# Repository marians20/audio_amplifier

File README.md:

# audio_amplifier

## PCB Manufacturing Providers

- [PCB Phoenix](https://phoenixpcb.ro/) – Au experiență solidă și pot produce circuite rigide, inclusiv plăci foarte lungi, de până la 2400 mm.

- [PCB-ELECTRA](https://www.pcb-electra.ro/) – Parte a Grupului ELECTRA, oferă plăci de circuite imprimate personalizate și are certificare UL.

- [Multi Circuit Boards](https://www.multi-circuit-boards.eu/en/index.html)

- [Price calculator](https://portal.multi-circuit-boards.eu/)

- Eashub – Oferă servicii complete, de la prototipuri la producție și asamblare PCB.

- PCBandAssembly – Se laudă cu livrare expres în 24 de ore și o politică de rambursare 100% pentru defecte de calitate

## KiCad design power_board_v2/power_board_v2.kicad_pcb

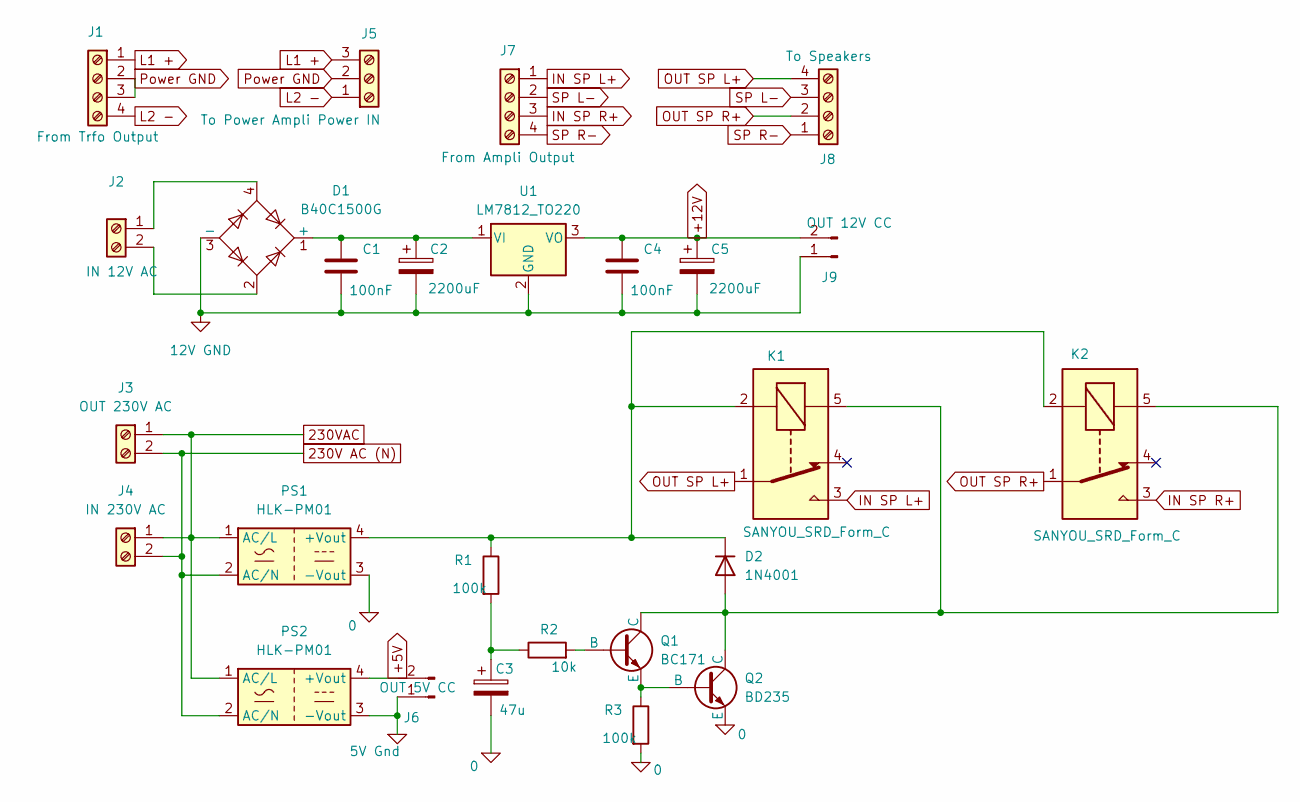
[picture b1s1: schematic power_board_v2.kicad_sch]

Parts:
C1, C4: 100nF; C_Disc_D8.0mm_W2.5mm_P5.00mm
C2, C5: 2200uF; CP_Radial_D12.5mm_P5.00mm
C3: 47u; CP_Radial_D5.0mm_P2.50mm
D1: B40C1500G; Diode_Bridge_Round_D9.8mm
D2: 1N4001; D_DO-41_SOD81_P10.16mm_Horizontal
J1: From Trfo Output; TerminalBlock_Altech_AK300-4_P5.00mm
J2: IN 12V AC; TerminalBlock_Altech_AK300-2_P5.00mm
J3: OUT 230V AC; TerminalBlock_Altech_AK300-2_P5.00mm
J4: IN 230V AC; TerminalBlock_Altech_AK300-2_P5.00mm
J5: To Power Ampli Power IN; TerminalBlock_Altech_AK300-3_P5.00mm
J6: OUT 5V CC; JST_XH_B2B-XH-A_1x02_P2.50mm_Vertical
J7: From Ampli Output; TerminalBlock_Altech_AK300-4_P5.00mm
J8: To Speakers; TerminalBlock_Altech_AK300-4_P5.00mm
J9: OUT 12V CC; JST_XH_B2B-XH-A_1x02_P2.50mm_Vertical
K1, K2: SANYOU_SRD_Form_C; Relay_SPDT_SANYOU_SRD_Series_Form_C
PS1, PS2: HLK-PM01; Converter_ACDC_Hi-Link_HLK-PMxx
Q1: BC171; TO-92L_Inline_Wide
Q2: BD235; TO-126-3_Vertical
R1, R3: 100k; R_Axial_DIN0207_L6.3mm_D2.5mm_P15.24mm_Horizontal
R2: 10k; R_Axial_DIN0207_L6.3mm_D2.5mm_P15.24mm_Horizontal
U1: LM7812_TO220; TO-220-3_Vertical

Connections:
0: C3.2, PS1.3 (-Vout), Q2.3 (E), R3.2
5V Gnd: J6.1, PS2.3 (-Vout)
12V GND: C1.2, C2.2, C4.2, C5.2, D1.3 (-), J9.1, U1.2 (GND)
230V AC (N): J3.2, J4.2, PS1.2 (AC/N), PS2.2 (AC/N)
230VAC: J3.1, J4.1, PS1.1 (AC/L), PS2.1 (AC/L)
+5V: J6.2, PS2.4 (+Vout)
+12V: C4.1, C5.1, J9.2, U1.3 (VO)
IN SP L+: J7.1, K1.3
IN SP R+: J7.3, K2.3
L1 +: J1.1, J5.3
L2 -: J1.4, J5.1
unnamed: C3.1, R1.2, R2.1
unnamed: C1.1, C2.1, D1.1 (+), U1.1 (VI)
unnamed: D2.2 (A), K1.5, K2.5, Q1.1 (C), Q2.1 (C)
unnamed: D2.1 (K), K1.2, K2.2, PS1.4 (+Vout), R1.1
unnamed: D1.4, J2.1
unnamed: D1.2, J2.2
unnamed: Q1.2 (B), R2.2
unnamed: Q1.3 (E), Q2.2 (B), R3.1
OUT SP L+: J8.4, K1.1
OUT SP R+: J8.2, K2.1
Power GND: J1.2, J1.3, J5.2
SP L-: J7.2, J8.3
SP R-: J7.4, J8.1

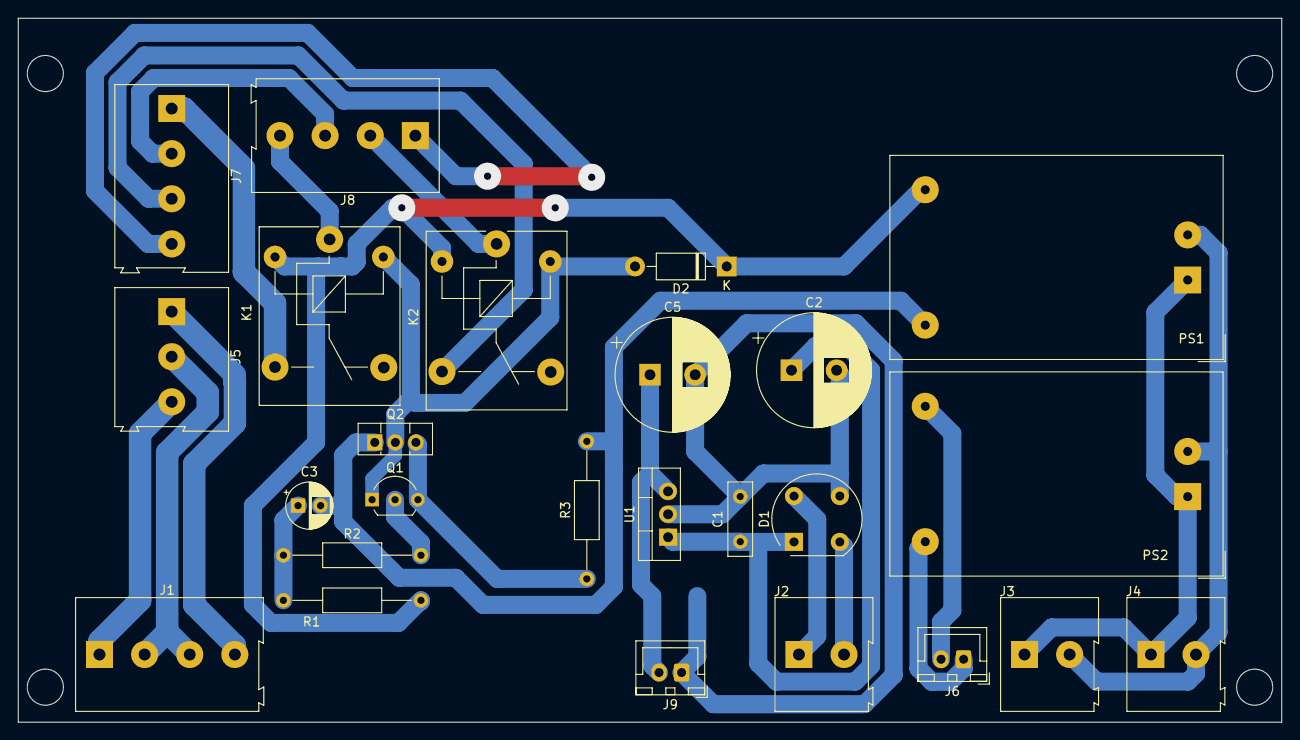
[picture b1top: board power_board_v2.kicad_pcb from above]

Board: 2 copper layers, 140.0 x 78.0 mm, 25 parts (0 on the bottom side), 24 nets.

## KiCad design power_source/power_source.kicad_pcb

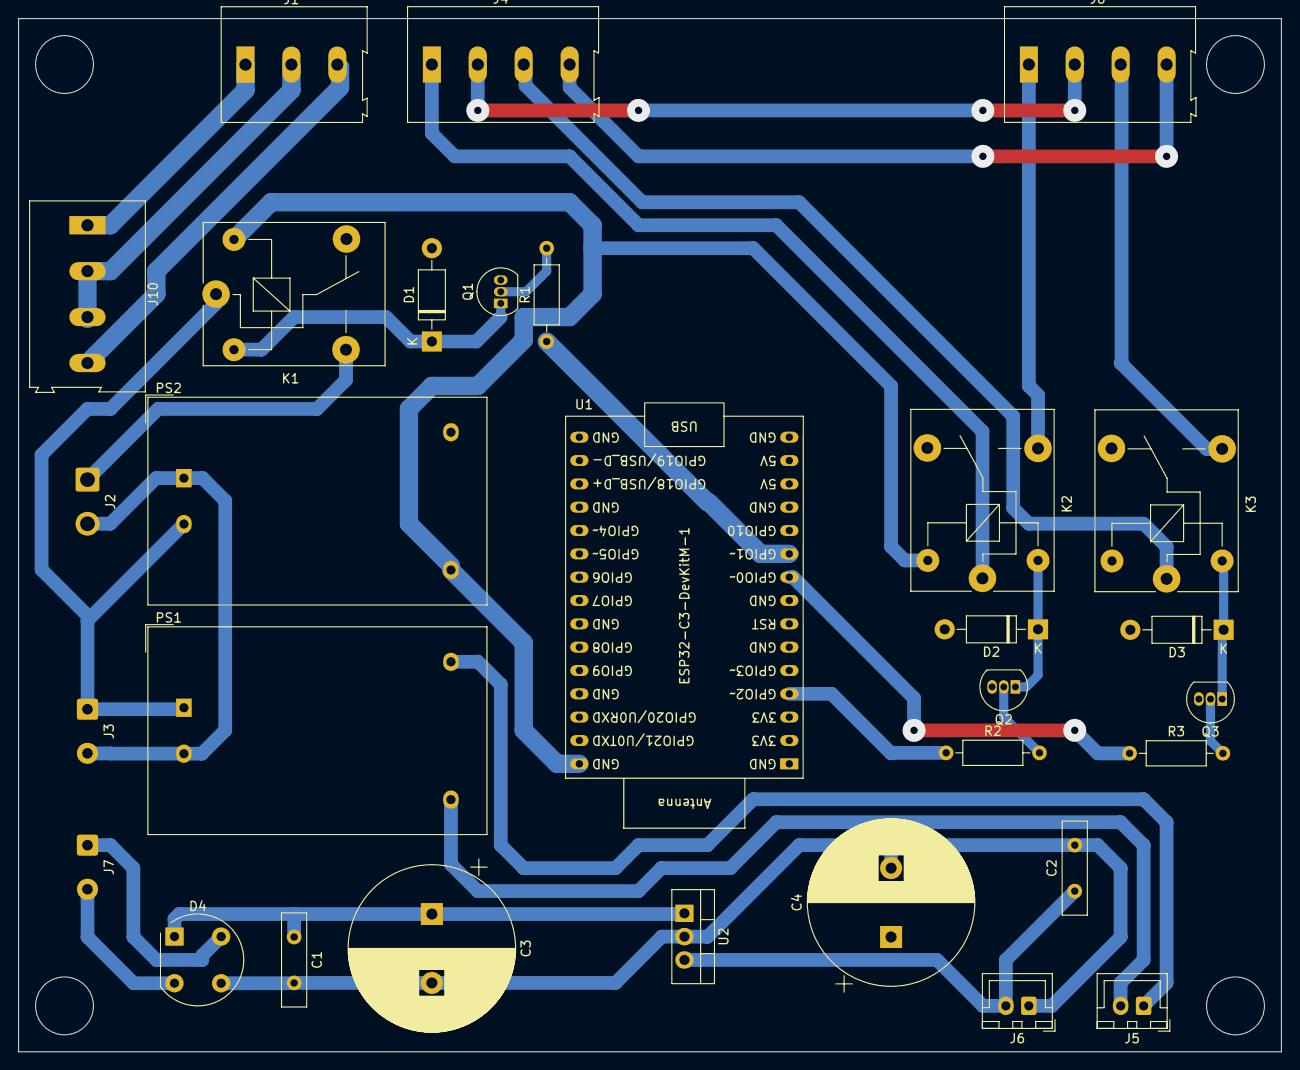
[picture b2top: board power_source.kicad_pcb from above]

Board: 2 copper layers, 137.5 x 112.5 mm, 30 parts (0 on the bottom side), 32 nets.

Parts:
C1, C2: 100nF; C_Disc_D10.0mm_W2.5mm_P5.00mm
C3, C4: 2200uF; CP_Radial_D18.0mm_P7.50mm
D1, D2, D3: 1N4001; D_DO-41_SOD81_P10.16mm_Horizontal
D4: B40C1500G; Diode_Bridge_Round_D9.8mm
J1: Power Ampli Power; TerminalBlock_Altech_AK300-3_P5.00mm
J2: Traf Primary; SolderWire-0.75sqmm_1x02_P4.8mm_D1.25mm_OD2.3mm
J3: Input 230V AC; SolderWire-0.5sqmm_1x02_P4.8mm_D0.9mm_OD2.3mm
J4: Power Ampl output; TerminalBlock_Altech_AK300-4_P5.00mm
J5: 5V DC; JST_XH_B2B-XH-A_1x02_P2.50mm_Vertical
J6: 12V DC; JST_XH_B2B-XH-A_1x02_P2.50mm_Vertical
J7: Input 12V AC; SolderWire-0.5sqmm_1x02_P4.8mm_D0.9mm_OD2.3mm
J8: Speakers; TerminalBlock_Altech_AK300-4_P5.00mm
J10: Trafo; TerminalBlock_Altech_AK300-4_P5.00mm
K1, K2, K3: SANYOU_SRD_Form_C; Relay_SPDT_SANYOU_SRD_Series_Form_C
PS1, PS2: HLK-PM01; Converter_ACDC_Hi-Link_HLK-PMxx
Q1, Q2, Q3: BC337; TO-92_Inline
R1, R2, R3: 10k; R_Axial_DIN0207_L6.3mm_D2.5mm_P10.16mm_Horizontal
U1: ESP32-C3-DevKitM-1
U2: LM7812_TO220; TO-220-3_Vertical

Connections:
3V3: U1.2 (3V3), U1.3 (3V3)
5V: U1.13 (5V), U1.14 (5V)
220V AC N: J2.2, J3.2, PS1.2 (AC/N), PS2.1 (AC/L)
220V AC R: J3.1, K1.1, PS1.1 (AC/L), PS2.2 (AC/N)
+5V: K1.5, K2.5, K3.5, PS2.4 (+Vout), U1.1 (GND), U1.6 (GND), U1.8 (GND), U1.12 (GND), U1.15 (GND), U1.16 (GND), U1.19 (GND), U1.24 (GND), U1.27 (GND), U1.30 (GND)
GND: D1.2 (A), D2.2 (A), D3.2 (A), PS2.3 (-Vout), Q1.3 (E), Q2.3 (E), Q3.3 (E)
IN LSP+: J4.1, K2.1
IN RSP+: J4.3, K3.1
unnamed: D1.1 (K), K1.2, Q1.1 (C)
unnamed: D2.1 (K), K2.2, Q2.1 (C)
unnamed: D3.1 (K), K3.2, Q3.1 (C)
unnamed: C1.1, C3.1, D4.1 (+), U2.1 (VI)
unnamed: C1.2, C2.2, C3.2, C4.2, D4.3 (-), J6.1, U2.2 (GND)
unnamed: J1.1, J10.1
unnamed: J1.2, J10.2, J10.3
unnamed: J1.3, J10.4
unnamed: J4.2, J8.2
unnamed: J4.4, J8.4
unnamed: J5.1, PS1.3 (-Vout)
unnamed: J5.2, PS1.4 (+Vout)
unnamed: C2.1, C4.1, J6.2, U2.3 (VO)
unnamed: D4.4, J7.1
unnamed: D4.2, J7.2
unnamed: Q1.2 (B), R1.2
unnamed: Q2.2 (B), R2.2
unnamed: Q3.2 (B), R3.2
OUT LSP+: J8.1, K2.3
OUT RSP+: J8.3, K3.3
REL1: R1.1, U1.10 (GPIO1)
REL2: R2.1, U1.4 (GPIO2)
REL3: R3.1, U1.9 (GPIO0)
Traf in: J2.1, K1.3

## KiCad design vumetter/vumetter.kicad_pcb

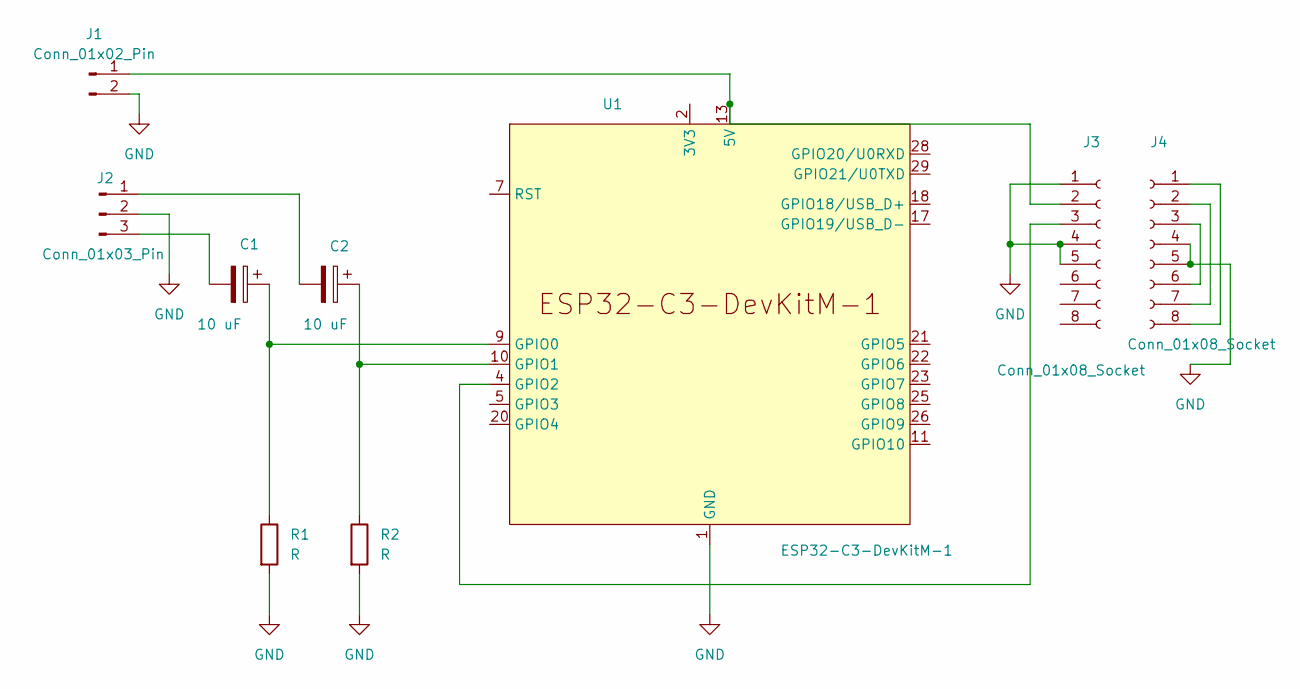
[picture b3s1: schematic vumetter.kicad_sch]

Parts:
C1, C2: 10 uF; CP_Radial_D6.3mm_P2.50mm
J1: Conn_01x02_Pin; JST_XH_B2B-XH-AM_1x02_P2.50mm_Vertical
J2: Conn_01x03_Pin; JST_XH_B3B-XH-AM_1x03_P2.50mm_Vertical
J3, J4: Conn_01x08_Socket; PinSocket_1x08_P2.54mm_Vertical
R1, R2: R; R_Axial_DIN0207_L6.3mm_D2.5mm_P10.16mm_Horizontal
U1: ESP32-C3-DevKitM-1

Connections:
3V3: U1.2 (3V3), U1.3 (3V3)
5V: J1.1, J3.2, U1.13 (5V), U1.14 (5V)
GND: J1.2, J2.2, J3.1, J3.4, J3.5, J4.4, J4.5, R1.2, R2.2, U1.1 (GND), U1.6 (GND), U1.8 (GND), U1.12 (GND), U1.15 (GND), U1.16 (GND), U1.19 (GND), U1.24 (GND), U1.27 (GND), U1.30 (GND)
unnamed: C2.2, J2.1
unnamed: C1.2, J2.3
unnamed: J3.3, U1.4 (GPIO2)
unnamed: J4.1, J4.8
unnamed: J4.2, J4.7
unnamed: J4.3, J4.6
unnamed: C1.1, R1.1, U1.9 (GPIO0)
unnamed: C2.1, R2.1, U1.10 (GPIO1)

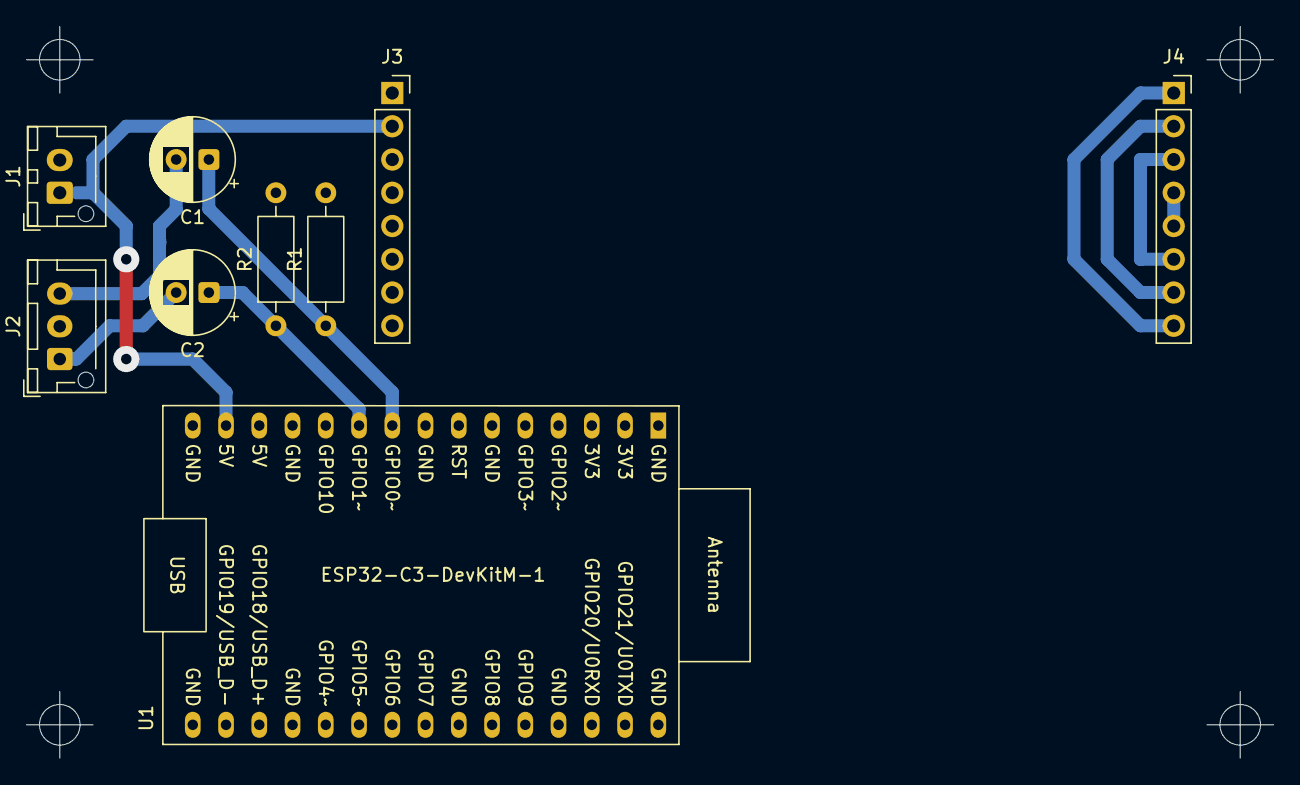
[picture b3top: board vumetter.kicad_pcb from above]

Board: 2 copper layers, 95.2 x 55.9 mm, 9 parts (0 on the bottom side), 11 nets.

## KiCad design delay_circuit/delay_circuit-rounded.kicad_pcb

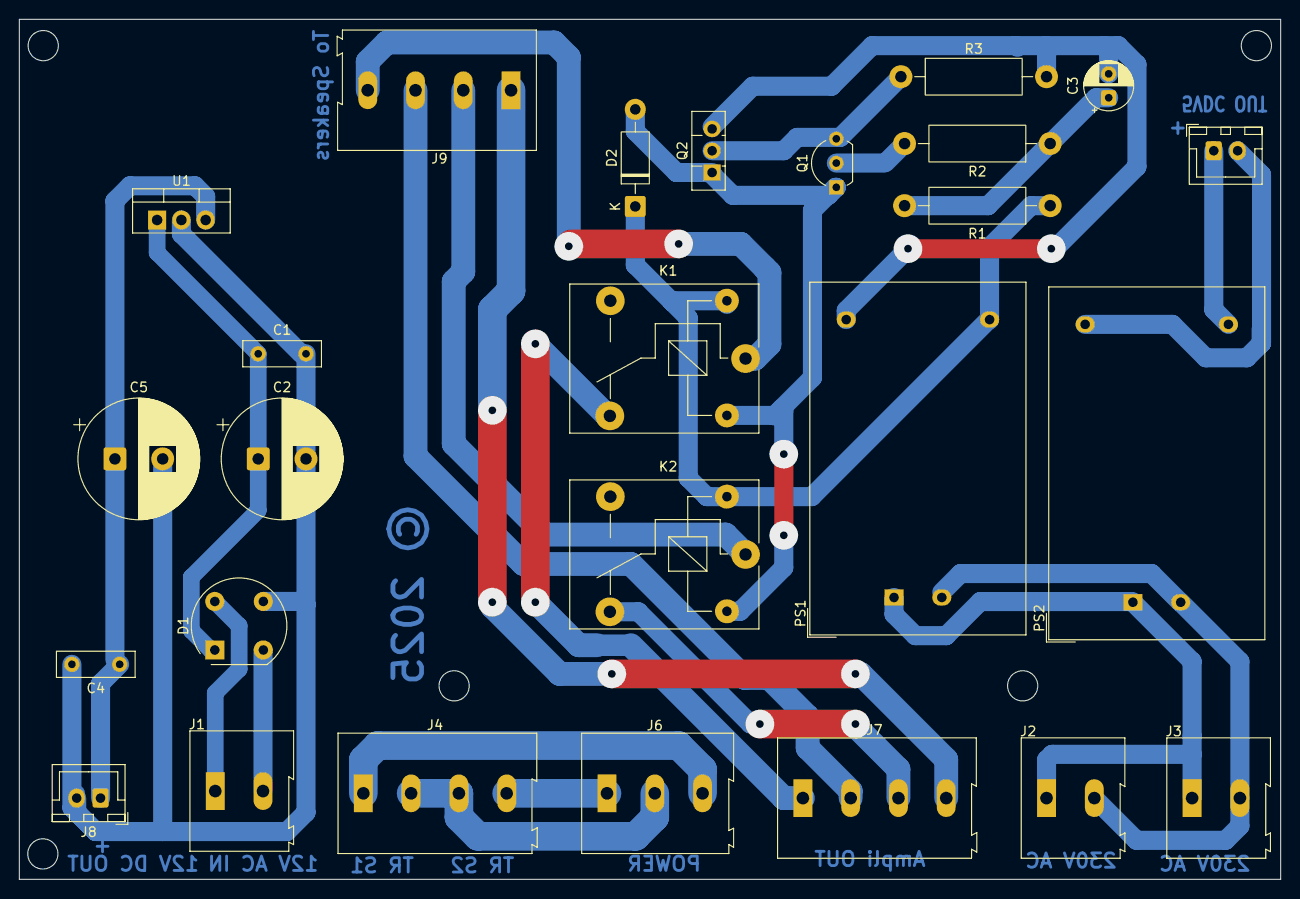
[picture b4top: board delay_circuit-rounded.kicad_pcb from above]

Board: 2 copper layers, 132.0 x 90.0 mm, 26 parts (0 on the bottom side), 24 nets.

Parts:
C1, C4: 100nF; C_Disc_D8.0mm_W2.5mm_P5.00mm
C2, C5: 2200uF; CP_Radial_D12.5mm_P5.00mm
C3: 47u; CP_Radial_D5.0mm_P2.50mm
D1: B40C1500G; Diode_Bridge_Round_D9.8mm
D2: 1N4001; D_DO-41_SOD81_P10.16mm_Horizontal
J1: IN 12V AC; TerminalBlock_Altech_AK300-2_P5.00mm
J2: OUT 230V AC; TerminalBlock_Altech_AK300-2_P5.00mm
J3: IN 230V AC; TerminalBlock_Altech_AK300-2_P5.00mm
J4: From Trfo Output; TerminalBlock_Altech_AK300-4_P5.00mm
J5: OUT 5V CC; JST_XH_B2B-XH-A_1x02_P2.50mm_Vertical
J6: To Power Ampli Power IN; TerminalBlock_Altech_AK300-3_P5.00mm
J7: From Ampli Output; TerminalBlock_Altech_AK300-4_P5.00mm
J8: OUT 12V CC; JST_XH_B2B-XH-A_1x02_P2.50mm_Vertical
J9: To Speakers; TerminalBlock_Altech_AK300-4_P5.00mm
K1, K2: SANYOU_SRD_Form_C; Relay_SPDT_SANYOU_SRD_Series_Form_C
PS1, PS2: HLK-PM01; Converter_ACDC_Hi-Link_HLK-PMxx
Q1: NPN; TO-92L_Inline_Wide
Q2: NPN; TO-126-3_Vertical
R1, R3: 100k; R_Axial_DIN0411_L9.9mm_D3.6mm_P15.24mm_Horizontal
R2: 10k; R_Axial_DIN0411_L9.9mm_D3.6mm_P15.24mm_Horizontal
U1: LM7812_TO220; TO-220-3_Vertical

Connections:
0: C3.2, PS1.3 (-Vout), Q2.3 (E), R3.2
12V GND: C1.2, C2.2, C4.2, C5.2, D1.3 (-), J8.2, U1.2 (GND)
IN SP L+: J7.1, K1.4
IN SP R+: J7.3, K2.4
unnamed: C3.1, R1.2, R2.1
unnamed: C1.1, C2.1, D1.1 (+), U1.1 (VI)
unnamed: D2.2 (A), K1.5, K2.5, Q1.1 (C), Q2.1 (C)
unnamed: D2.1 (K), K1.2, K2.2, PS1.4 (+Vout), R1.1
unnamed: D1.4, J1.1
unnamed: D1.2, J1.2
unnamed: J2.1, J3.1, PS1.1 (AC/L), PS2.1 (AC/L)
unnamed: J2.2, J3.2, PS1.2 (AC/N), PS2.2 (AC/N)
unnamed: J4.1, J6.3
unnamed: J4.2, J4.3, J6.2
unnamed: J4.4, J6.1
unnamed: J5.1, PS2.4 (+Vout)
unnamed: J5.2, PS2.3 (-Vout)
unnamed: J7.2, J9.3
unnamed: J7.4, J9.1
unnamed: C4.1, C5.1, J8.1, U1.3 (VO)
unnamed: Q1.2 (B), R2.2
unnamed: Q1.3 (E), Q2.2 (B), R3.1
OUT SP L+: J9.4, K1.1
OUT SP R+: J9.2, K2.1

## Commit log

2025-05-17 Done dela circuit
2025-05-17 Fixed issues in source
2025-05-18 working on power board
2025-05-18 Updated board
2025-05-18 Rounded corners and undone.
2025-05-18 Improved PCB.
2025-05-20 Improved board.
2025-05-20 Reduced board size.
2025-05-24 Power board.
2025-05-25 Blutettoh receiver
2025-06-05 Added embedded projects.
2025-06-05 Removed build folder
2025-06-05 Trobuleshooting missing of output from DAC.
2025-06-05 try to improve BT receiver.
2025-06-13 Added arduino audio pocs.
2025-06-13 Improved media_player3. Added vumeter functionality.
2025-06-13 Imporved vumeter.
2025-06-17 Vumeter tunning.

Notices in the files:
delay_circuit/delay_circuit-rounded.kicad_pcb:
© 2025
